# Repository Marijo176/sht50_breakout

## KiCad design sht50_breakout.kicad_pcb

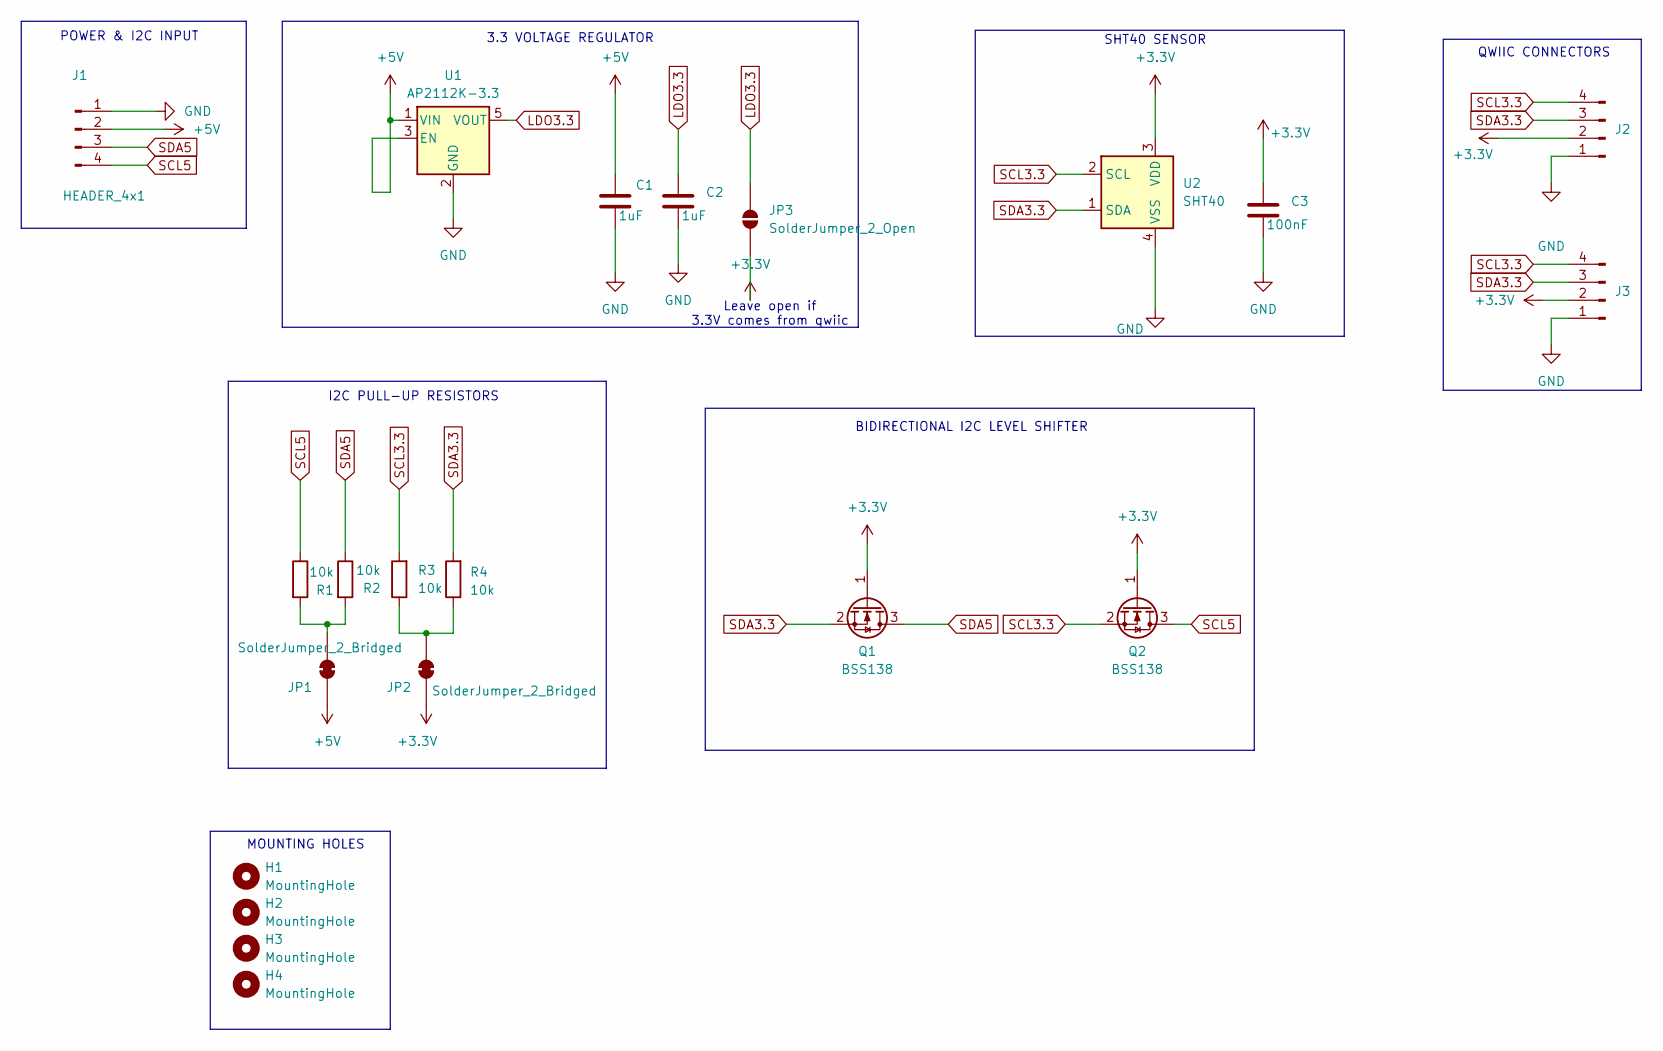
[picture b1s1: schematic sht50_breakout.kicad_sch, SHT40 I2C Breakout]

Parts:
C1, C2: 1uF; C_0603_1608Metric
C3: 100nF; C_0603_1608Metric
H1, H2, H3, H4: MountingHole; MountingHole_2.1mm
J1: HEADER_4x1; PinHeader_1x04_P2.54mm_Vertical
J2, J3: SM04B-SRSS-TB; JST_SH_SM04B-SRSS-TB_1x04-1MP_P1.00mm_Horizontal
JP1, JP2: SolderJumper_2_Bridged; SolderJumper-2_P1.3mm_Bridged2Bar_Pad1.0x1.5mm
JP3: SolderJumper_2_Open; SolderJumper-2_P1.3mm_Open_Pad1.0x1.5mm
Q1, Q2: BSS138; SOT-23
R1, R2, R3, R4: 10k; R_0603_1608Metric
U1: AP2112K-3.3; SOT-23-5
U2: SHT40; Sensirion_DFN-4_1.5x1.5mm_P0.8mm_SHT4x_NoCentralPad

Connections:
+3.3V: C3.1, J2.2, J3.2, JP2.2 (B), JP3.1 (A), Q1.1 (G), Q2.1 (G), U2.3 (VDD)
+5V: C1.1, J1.2, JP1.2 (B), U1.1 (VIN), U1.3 (EN)
GND: C1.2, C2.2, C3.2, J1.1, J2.1, J3.1, U1.2 (GND), U2.4 (VSS)
LDO3.3: C2.1, JP3.2 (B), U1.5 (VOUT)
unnamed: JP1.1 (A), R1.2, R2.2
unnamed: JP2.1 (A), R3.1, R4.1
SCL3.3: J2.4, J3.4, Q2.2 (S), R3.2, U2.2 (SCL)
SCL5: J1.4, Q2.3 (D), R1.1
SDA3.3: J2.3, J3.3, Q1.2 (S), R4.2, U2.1 (SDA)
SDA5: J1.3, Q1.3 (D), R2.1

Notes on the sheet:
I2C PULL-UP RESISTORS
Leave open if 3.3V comes from qwiic
3.3 VOLTAGE REGULATOR
MOUNTING HOLES
QWIIC CONNECTORS
POWER & I2C INPUT
BIDIRECTIONAL I2C LEVEL SHIFTER
SHT40 SENSOR

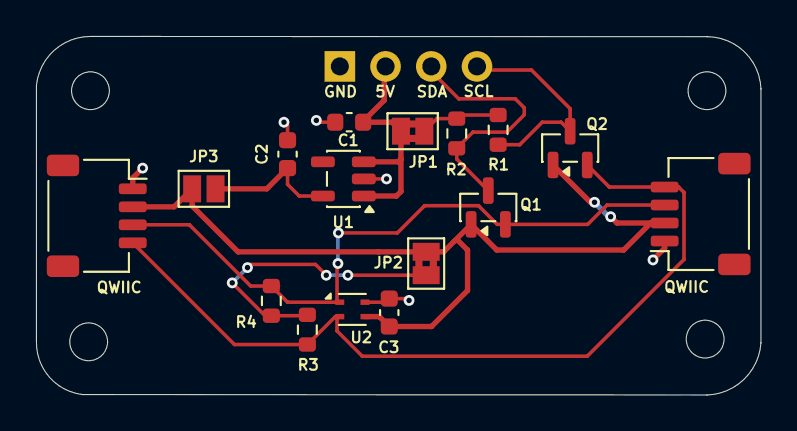
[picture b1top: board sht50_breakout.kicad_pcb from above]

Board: 2 copper layers, 40.2 x 19.9 mm, 21 parts (0 on the bottom side), 10 nets.
